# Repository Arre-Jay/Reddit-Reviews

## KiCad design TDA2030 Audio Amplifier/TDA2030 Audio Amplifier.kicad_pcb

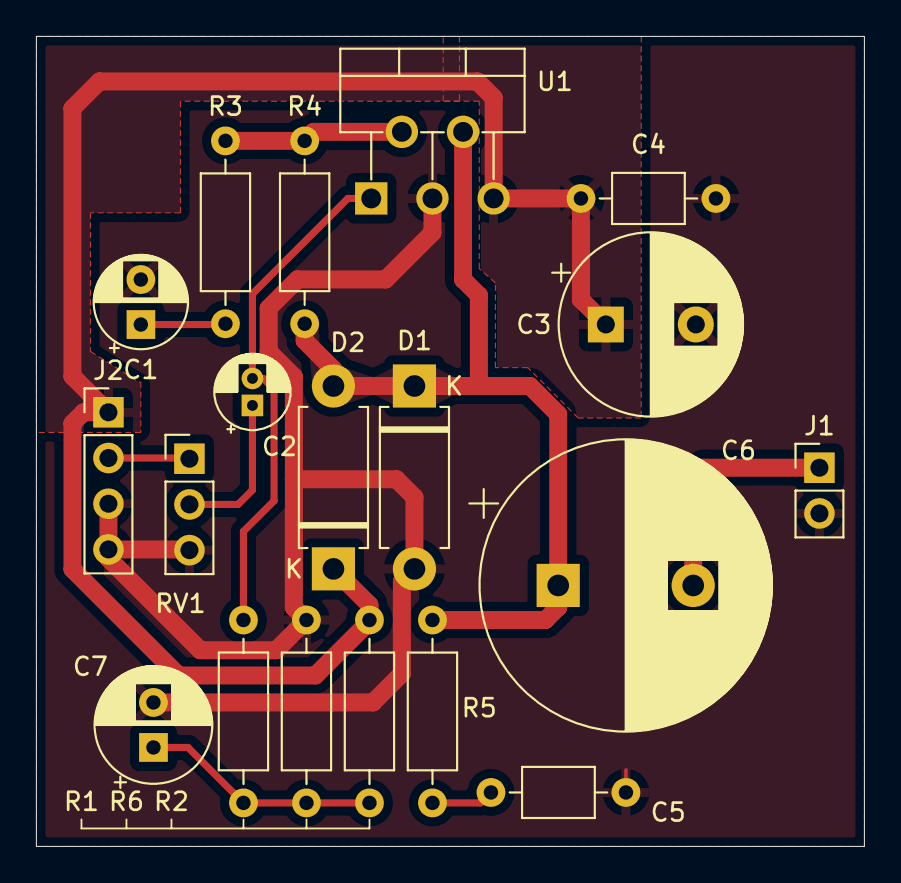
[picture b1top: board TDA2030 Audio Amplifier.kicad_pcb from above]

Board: 2 copper layers, 46.0 x 45.0 mm, 19 parts (0 on the bottom side), 11 nets.

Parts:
C1: 10uF; CP_Radial_D5.0mm_P2.50mm
C2: 2.2uF; CP_Radial_D4.0mm_P1.50mm
C3: 220uF; CP_Radial_D10.0mm_P5.00mm
C4, C5: 220nF; C_Axial_L3.8mm_D2.6mm_P7.50mm_Horizontal
C6: 2200uF; CP_Radial_D16.0mm_P7.50mm
C7: 22uF; CP_Radial_D6.3mm_P2.50mm
D1, D2: 1N4001; D_DO-15_P10.16mm_Horizontal
J1: 8Ohm Speaker; PinHeader_1x02_P2.54mm_Vertical
J2: INPUT; PinHeader_1x04_P2.54mm_Vertical
R1, R2, R6: 100K; R_Axial_DIN0207_L6.3mm_D2.5mm_P10.16mm_Horizontal
R3: 3K3; R_Axial_DIN0207_L6.3mm_D2.5mm_P10.16mm_Horizontal
R4: 30K; R_Axial_DIN0207_L6.3mm_D2.5mm_P10.16mm_Horizontal
R5: 1R; R_Axial_DIN0207_L6.3mm_D2.5mm_P10.16mm_Horizontal
RV1: 10K; PinHeader_1x03_P2.54mm_Vertical
U1: TDA2030; TO-220-5_P3.4x3.7mm_StaggerOdd_Lead3.8mm_Vertical

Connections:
GND: C1.2, C3.2, C4.2, C5.2, C7.2, D1.2 (A), J1.2, J2.3, J2.4, R1.2, RV1.3, U1.3 (-Vs)
unnamed: C1.1, R3.2
unnamed: C2.1, RV1.2
unnamed: C5.1, R5.2
unnamed: C7.1, R1.1, R2.2, R6.2
unnamed: C6.1, D1.1 (K), D2.2 (A), R4.2, R5.1, U1.4
unnamed: C6.2, J1.1
unnamed: J2.2, RV1.1
unnamed: C2.2, R6.1, U1.1 (+)
unnamed: R3.1, R4.1, U1.2 (-)
VCC: C3.1, C4.1, D2.1 (K), J2.1, R2.1, U1.5 (+Vs)

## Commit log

2024-12-13 Updated Schematic
2025-01-21 Added TDA2030 Project
2025-01-22 Updated Vcc tracks.
